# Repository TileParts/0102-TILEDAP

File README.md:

0102-TILEDAP
==========

一个 DAPLink 调试器，附带 USB-UART 桥接功能。

## 特性

1. 使用 STM32F103TBU6 小封装
2. 实体 nRESET 键，用于复位目标 MCU，或长按进入 TILEDAP 自身的拖拽更新模式
3. 引出了一对 UART TX/RX，可通过免驱的 USB CDC-ACM 读取目标 MCU 串口日志

## 协议

[CERN-OHL-P-2.0](LICENSE)

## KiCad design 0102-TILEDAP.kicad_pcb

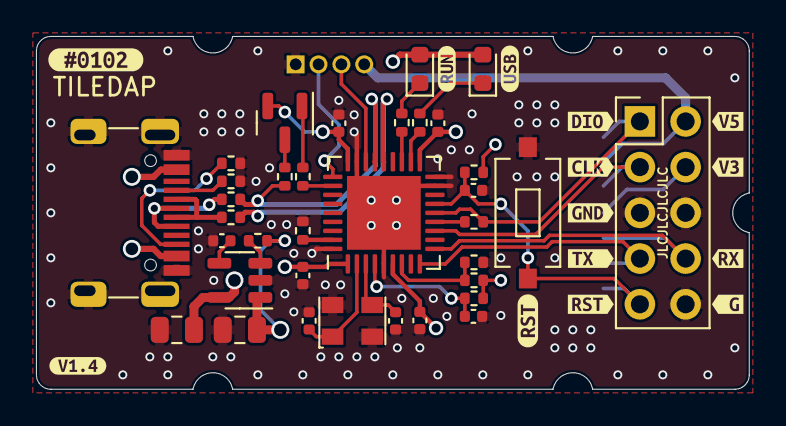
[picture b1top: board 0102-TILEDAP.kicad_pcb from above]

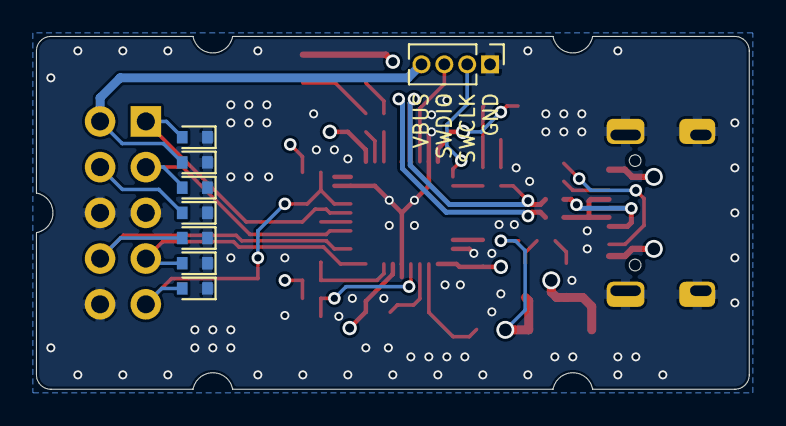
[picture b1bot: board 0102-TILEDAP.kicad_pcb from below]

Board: 4 copper layers, 39.6 x 19.6 mm, 57 parts (8 on the bottom side), 31 nets.

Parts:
C1, C3: 10uF/25V; C_0805_2012Metric
C2: 10nF; C_0402_1005Metric
C4, C5, C6, C7, C12, C13: 100nF; C_0402_1005Metric
C8, C11: 22pF; C_0402_1005Metric
D1: BLUE; LED_0603_1608Metric
D3: RED; LED_0603_1608Metric
D7: LESD5Z5.0CT1G; D_SOD-523
D?: LESD5Z5.0CT1G; D_SOD-523
D?#2, D?#3, D?#4, D?#5, D?#6: LESD5Z5.0CT1G; D_SOD-523
J1: USB-C; HRO_TYPE-C-31-M-12
J2: IF; PinHeader_1x04_P1.27mm_Vertical
J3: TGT; PinHeader_2x05_P2.54mm_Vertical
Q1: S8550; SOT-23
R1, R3: 5.1K; R_0402_1005Metric
R2, R12: 10K; R_0402_1005Metric
R4, R5: 0R; R_0402_1005Metric
R6, R7: 4.7K; R_0402_1005Metric
R8, R13: 100K; R_0402_1005Metric
R9: 100R; R_0402_1005Metric
R10, R14: 1.5K; R_0402_1005Metric
R11: 220R; R_0402_1005Metric
R15: 470R; R_0402_1005Metric
SW1: SW_Push; HCTL_TC-3601L-2.5
U1: SPX3819M5-L-3-3; SOT-23-5
U2: STM32F103TBU6; QFN-36-1EP_6x6mm_P0.5mm_EP4.1x4.1mm
Y1: 8MHz; Oscillator_SMD_3.2x2.5mm
kibuzzard-631DD70B: G***; kibuzzard-631DD70B
kibuzzard-631DD701: G***; kibuzzard-631DD701
kibuzzard-631DD707: G***; kibuzzard-631DD707
kibuzzard-631DDA4D: G***; kibuzzard-631DDA4D
kibuzzard-632A8CA6: G***; kibuzzard-632A8CA6
kibuzzard-632952D1: G***; kibuzzard-632952D1
kibuzzard-632952D9: G***; kibuzzard-632952D9
kibuzzard-632952DE: G***; kibuzzard-632952DE
kibuzzard-632952E3: G***; kibuzzard-632952E3
kibuzzard-632952EA: G***; kibuzzard-632952EA
kibuzzard-6329514A: G***; kibuzzard-6329514A
kibuzzard-63295172: G***; kibuzzard-63295172
kibuzzard-63295177: G***; kibuzzard-63295177
kibuzzard-63295187: G***; kibuzzard-63295187

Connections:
+3V3: C3.2, C4.2, C5.2, C6.2, C7.2, D1.2 (A), D3.2 (A), D?#4.2 (A2), J3.4, Q1.2 (E), R6.1, R12.2, R13.2, U1.5 (OUT), U2.1 (VDD), U2.6 (VDDA), U2.19 (VDD), U2.27 (VDD)
/D+: J1.A6 (D+), J1.B6 (D+), R5.2
/D-: J1.A7 (D-), J1.B7 (D-), R4.2
/IF_NRESET: C13.2, R13.1, U2.4 (NRST)
/IF_SWCLK: J2.2, U2.28 (PA14)
/IF_SWDIO: J2.3, U2.25 (PA13)
/LED_CON_BLUE: R11.1, U2.20 (PA8)
/LED_RUN_RED: R15.1, U2.21 (PA9)
/TGT_NRESET: C12.2, D?.2 (A2), J3.9, R12.1, SW1.2, U2.15 (PB0)
/TGT_RX: D7.2 (A2), J3.8, U2.10 (PA3)
/TGT_SWCLK: D?#2.2 (A2), J3.3, U2.12 (PA5)
/TGT_SWDIO: D?#6.2 (A2), J3.1, R9.1, U2.14 (PA7)
/TGT_TX: D?#5.2 (A2), J3.7, U2.9 (PA2)
/TGT_USB_D+: R5.1, R10.2, U2.24 (PA12)
/TGT_USB_D-: R4.1, U2.23 (PA11)
/USB_ENUM: R14.1, U2.29 (PA15)
GND: C1.1, C2.1, C3.1, C4.1, C5.1, C6.1, C7.1, C8.1, C11.1, C12.1, C13.1, D7.1 (A1), D?.1 (A1), D?#2.1 (A1), D?#3.1 (A1), D?#4.1 (A1), D?#5.1 (A1), D?#6.1 (A1), J1.A1 (GND), J1.A12 (GND), J1.B1 (GND), J1.B12 (GND), J1.S1 (SHIELD), J2.1, J3.5, J3.6, J3.10, R1.1, R3.1, R7.1, R8.2, SW1.1, U1.2 (GND), U2.5 (VSSA), U2.17 (PB2), U2.18 (VSS), U2.26 (VSS), U2.36 (VSS), U2.37 (VSS), Y1.2, Y1.4
unnamed: C2.2, U1.4 (BP)
unnamed: C8.2, U2.3 (PD1), Y1.3
unnamed: C11.2, U2.2 (PD0), Y1.1
unnamed: D1.1 (K), R11.2
unnamed: D3.1 (K), R15.2
unnamed: J1.A5 (CC1), R1.2
unnamed: J1.B5 (CC2), R3.2
unnamed: Q1.1 (B), R14.2
unnamed: Q1.3 (C), R10.1
unnamed: R2.1, U1.3 (EN)
unnamed: R6.2, R7.2, U2.7 (PA0)
unnamed: R8.1, U2.35 (BOOT0)
unnamed: R9.2, U2.13 (PA6)
VBUS: C1.2, D?#3.2 (A2), J1.A4 (VBUS), J1.A9 (VBUS), J1.B4 (VBUS), J1.B9 (VBUS), J2.4, J3.2, R2.2, U1.1 (IN)

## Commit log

2022-09-07 Init repository
2022-09-08 Set up repository
2022-09-08 Add #0102 DAPLink
2022-09-08 Update DAPLink to 4-layers
2022-09-08 Finish DAPLink with final outline
2022-09-08 Output gerber for DAPLink V1.0
2022-09-08 Import 3D models for DAPLink
2022-09-08 Correct silks
2022-09-08 Fix USB enumerate
2022-09-08 Output gerber V1.1
2022-09-08 Add README
2022-09-12 Migrate to KiCad 6
2022-09-12 Rework silks
2022-09-12 Fix models
2022-09-12 Update rendered image
2022-09-13 Refill copper to fix shield pin of USB-C connector
2022-09-16 Update resistor for LED_CON_BLUE
2022-09-16 Fix USB_ENUM
2022-09-16 MFDoc V1.3
2022-09-22 Rework PCB
    * Use New boundary
    * Use laid USB-C connector
    * Add ESDs
2022-09-22 MFDoc V1.4
2022-09-29 Fix duplicated properties of sch
